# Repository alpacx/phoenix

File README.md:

# Phoenix — gateway multi-piattaforma

Gateway sperimentale, non ancora un prodotto validato. Backend ESP32 esistente;
backend Linux per ROCK 4C+ implementato in forma sperimentale e testato in Docker. La sezione hardware/build sotto descrive
ESP32; per Linux consultare il relativo README e le verifiche disponibili.

## Organizzazione

- [ESP32 / ESP-IDF](platforms/esp32/README.md): sorgenti in `platforms/esp32/main/`.
- [Linux / ROCK](platforms/linux/README.md): backend Linux, istruzioni e stato delle verifiche.
- `shared/web/`: pannello amministrativo comune.
- `shared/phoenix_core/`: logica C portabile.
- [Mappa del progetto](docs/PROJECT_STRUCTURE.md) e [istruzioni agenti](AGENTS.md).
- `hardware/phoenix-g1/`: progettazione della scheda custom, ancora incompleta.

Implementati: Ethernet IP101/RMII con DHCP, USB HS CDC-NCM con DHCP/NAT IPv4,
firewall L3/L4, API amministrativa locale e pannello, importatore WireGuard IPv4
full tunnel e blocco in uscita, gestione C6 STA/AP e aggiornamento firmato in software. La presenza del codice e una build riuscita non
provano il funzionamento sul banco: consultare PROGRESS.md.

## Build

ESP-IDF 5.5.4, commit esatto `10ca0dff2f40aeb539f22d1ef88d031cf7421743`.
Dipendenze registry e relativi hash in dependencies.lock. Toolchain installata:
`riscv32-esp-elf esp-14.2.0_20260121`. Script configurato per l'ambiente locale;
IDF_PATH e IDF_PYTHON_ENV_PATH sono sovrascrivibili.

```sh
./tools/test.sh
# Scheda rilevata v3.1; USB dati spento:
./tools/build.sh -B build-rev3 -D SDKCONFIG=build-rev3/sdkconfig \
  -D 'SDKCONFIG_DEFAULTS=sdkconfig.defaults;sdkconfig.rev3'
# Solo compilazione del percorso USB, NON certifica il cablaggio:
./tools/build.sh -B build-usb-rev3 -D SDKCONFIG=build-usb-rev3/sdkconfig \
  -D 'SDKCONFIG_DEFAULTS=sdkconfig.defaults;sdkconfig.rev3;sdkconfig.lab;sdkconfig.signed'
```

La variante firmata richiede prima la chiave descritta in [OTA](docs/OTA.md).

Il default sdkconfig.defaults supporta P4 v1.x; non caricarlo sulla v3.1.
Per una build USB di banco v3.x aggiungere sdkconfig.lab DOPO sdkconfig.rev3
in una cartella di build nuova. Non modificare i file SDK globali.

## Cablaggio e flash

Leggere [HARDWARE.md](docs/HARDWARE.md). La USB-C è seriale/alimentazione; la
Type-A è OTG e porta VBUS generata dalla scheda. Non collegare un generico
cavo host-host. USB dati resta disattivata per default.

Il backup originale è locale, riservato e ignorato da Git:
`results/recovery/original-flash.bin`. Non distribuirlo: può contenere dati
preesistenti. Per ripristinare, dopo aver identificato nuovamente la stessa
scheda e verificato hash/dimensione:

```sh
# Da ambiente ESP-IDF attivato. PORT deve essere la P4 dedicata identificata.
python -m esptool --chip esp32p4 --port "$PORT" write_flash 0 results/recovery/original-flash.bin
```

Non modificare eFuse. Nessuna flash encryption/secure boot irreversibile attivata.
BOOT+RESET è la via ROM di recupero; BOOT condivide GPIO35 con Ethernet TXD1:
non usarlo come pulsante dell'interfaccia durante il traffico.

## Uso sperimentale

USB LAN: 192.168.7.1/24, DHCP, pannello http://192.168.7.1/. Nessun servizio
amministrativo accettato dall'uplink. Pairing via UART nei primi 120 secondi:
`pair ` seguito da 64 caratteri esadecimali casuali, mai riportati nei log.
Il token rimane solo nel client; la scheda conserva SHA-256 in NVS.
`time <epoch UNIX di 10 cifre>` imposta l'orologio nello stesso intervallo.
Il pannello conserva il token nella sessionStorage della scheda browser e lo elimina al logout.

All'avvio il traffico inoltrato è bloccato. La modalità diretta è una scelta
esplicita via API. WireGuard resta chiuso finché non esiste una sessione valida.
Il dispositivo non controlla il traffico del Mac sulle altre interfacce.
Non è un antivirus, un IDS completo o uno strumento di ispezione HTTPS.

[API](docs/API.md) · [Architettura](docs/ARCHITECTURE.md) ·
[Prove](docs/TESTING.md) · [Dipendenze](docs/DEPENDENCIES.md) ·
[Attività](TASKS.md) · [Ripresa](NEXT_SESSION.md)

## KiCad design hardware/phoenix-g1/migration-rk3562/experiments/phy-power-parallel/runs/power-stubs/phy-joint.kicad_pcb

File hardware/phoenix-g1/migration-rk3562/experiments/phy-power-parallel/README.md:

# PHY joint SW geometry — isolated, electrically unqualified

This experiment freezes compact-corridor source `21c11942a68f62c506769caed42e84f3358d85e159f8b7bc2ba2f87e9014b30f`. No main board, main checkpoint or original compact study was modified.

`checkpoint.json` selects joint-002 for **geometry study only**. Its SW trunk and output branch remain 1.55 mm, clearance rules remain unchanged, input corridor remains 1.05 mm. RXCLK resistor return is relocated to the already-tested main-route corridor ending at (66.15,30.125), maintaining 0.20 mm track and 0.45/0.20 mm via. The output branch termination is offset 0.15 mm within L501 pad 2; this removes the 0.10 mm inter-branch clearance failure without narrowing either branch.

Joint-001 exposed a further clearance to U5 NC pad31 (0.0735 mm). Joint-002 moves the broad SW trunk outward/upward and extends the existing exploratory pin fanout. This removes all new DRC errors, but the 0.20 mm QFN neck is 0.707 mm long and **does not satisfy the historical >60 mil whole-path guidance**. No permission/derogation to that guidance is inferred. Do not promote this route as qualified power layout.

Verification: zero new DRC violations; 2,006 pad instances and 5,810 unreplaced tracks/vias preserved; 71 original connected pad groups preserved; no new mechanical reservation conflicts. U5.30→L501.1, L501.2→C511.1, R522.2→C515.2 and C515.1→C517.1 connectivity passes. Six subprocess tests exercise nominal routes, intentional width reductions, SW/output disconnections and mandatory qualification hold.

Rebuild with KiCad Python:

```
python3 hardware/phoenix-g1/tools/parallel_phy_sw_joint.py --case joint-rebuild
python3 hardware/phoenix-g1/tools/parallel_phy_test_joint.py
```

Use KiCad bundled Python, not generic system Python. Test script checks frozen joint-002 hash; rebuild receives new UUIDs and has its own report. Each report compares actual geometry with the frozen baseline. Existing baseline DRC items remain; “zero new” does not mean production-ready.

Remaining electrical holds: applicable Realtek fanout guidance, compact inductor saturation/DCR/ripple, effective C515 capacitance at 3.3 V (component review indicates strong DC bias reduction), and remaining input/load feeds. No simulation or physical test has been performed. No BOM adoption, purchase or manufacturing release.

## Follow-up component and feed probes

`variant-16v.json` records a second geometry-passing, six-test-passing candidate using CL10A475KO8NNNC (C19666) for C515, with unchanged 0603 footprint. Component-review Samsung numeric curves indicate 3.2694 µF typical at 3.3 V; this is an improvement over approximately 2.10 µF for C1705, **not** a guaranteed effective minimum or validation of regulator stability. Rebuild using `--bulk-16v --case joint-16v-rebuild`. Test via `PHOENIX_PHY_TEST_VARIANT=joint-16v`.

The 0805 candidate CL21A475KAQNNNE (C1779) was physically substituted in `runs/joint-0805` and rejected: GND copper at y=23.3 and courtyards R509/R1002/R516 interfere. Do not treat it as a drop-in. `bulk-0805-review.json` lists the required surrounding layout changes.

Two explicitly drawn full-width F.Cu feed candidates are retained as rejected evidence: `feed-front` (R530 to C515,1.05 mm,19 new violations) and `load-front` (C511 to C512,1.55 mm,84 new violations). These specific paths intersect existing oscillator, buck feedback, bypass and strap copper. They do not prove that all possible F.Cu paths are impossible. Do not repeat them or adopt them. `parallel_phy_feed_probe.py` reproduces both without modifying the baseline or reducing widths.

## Post-inductor distribution geometry

`load-checkpoint.json` records C511.1→C512.1 continuity via a full 1.55 mm In3.Cu corridor and two 0.60/0.30 mm through vias at each end. The north2 path avoids the CPU via at (56.5,28.5) found by the north1 probe; the southern path remains rejected due to oscillator/ground vias. No new traces are placed on In1/In4 ground planes. Zero new DRC violations, all 5,822 incoming copper items and 72 connected pad groups preserved, no new mechanical conflicts. Six tests include width reduction, cutting either via array, ground-plane role and mandatory qualification holds.

This is **post-inductor distribution**, not a relaxation of the unresolved REG_OUT/DVDD33 local no-via/width guidance. Via current capacity, power integrity, return paths, thermal performance and pad-overlap/filled-via assembly requirements remain unqualified. No fabrication release. `parallel_phy_feed_probe.py load-in3-north2` rebuilds this geometry; `parallel_phy_test_load.py` checks it.

### Additional bypasses

`load-c514-checkpoint.json`: extends the In3 1.55 mm distribution to C514/U5.21, with two 0.60/0.30 mm load vias. Six tests pass; zero new DRC, all incoming copper preserved. The earlier y=29.0/29.1 paths fail against the RXCLK GND via; final trunk y=28.9 gives 0.225 mm nominal clearance.

`load-c513-checkpoint.json`: moves previously disconnected C513 from its remote position to (65.4,34.5), beside U5.8, preserving pad identities and nets. Replaces only its two explicitly identified disconnected ground-stub segments. Adds the 1.55 mm In3 branch and two 0.60/0.30 mm vias, a 0.20 mm F.Cu pin fanout, and a 0.20 mm local GND return with a 0.45/0.20 mm via. Both C513 terminals are verified connected, including U5.8→C513.1 and C513.2→existing GND. Zero new DRC and six tests pass; mandatory fanout/current/PI/via-overlap holds remain. Courtyard placement is tight between U5 and U22; manufacturability remains to be reviewed. The rejected vertical and first horizontal placements are retained in c513/c513b reports.

No main/BOM adoption has occurred. The latest geometry candidate is an isolated study, not a replacement for the main checkpoint. C522/U5.38 and upstream input feed remain incomplete.

## Rebuild and C522 blockers

`rebuild-verification.json` confirms a fresh C513d rebuild matches all footprint identities/placements, pad UUIDs/nets/sizes and track/via geometry (generated copper UUIDs and zone serialization excluded). Fresh DRC/preservation/connectivity also pass. Rebuild does not overwrite the selected study: set `PHOENIX_PHY_OUTPUT_CASE=rebuild-c513d` when calling its builder.

C522 studies `c522-clock` and `c522-clock2` remain rejected. The first relocates the capacitor behind the board and replaces XOUT, but collides with Y501 pad, the existing +5V_MAIN trunk on In2, and clock copper. The second also replaces the B.Cu XIN branch at its original 0.20 mm width; single-via escape and broad power still collide with the local ground/clock corridor. Neither candidate is selected. Clock loading/loop geometry and any changed via strategy would require qualification even after geometric success. Moving C511 local return or the upstream 5V corridor would be a broader joint change; no such change was made here.

## Sequential continuation — 18 November, 16V bulk carried forward

`load-c513-16v-checkpoint.json` is the latest isolated geometry variant. It carries the previously studied C515 CL10A475KO8NNNC into the C513 bypass/distribution candidate. No copper geometry or footprint placement changes were made in this variant. DRC introduces no violations; preservation and nine required connectivity checks pass. Six load tests pass, including deliberate route narrowing and disconnections. Current public C19666 lookup: $0.015, presale 2503304 / overseas 3310825; not assembly allocation. Typical 3.2694uF at 3.3V is not a guaranteed minimum or stability qualification. No main-board/BOM adoption.

New `input-in2-001` upstream feed probe was rejected: full 1.05mm inner route collides with +3V3_IO and WIFI_BUCK_OUT; entry/exit also collide with the oscillator ground and CPU_BUCK_EN. Do not run the untried `input-in2-002` as a proposed fix: moving the middle path does not solve endpoint conflicts. The input needs a joint redesign of the existing R530 entry and C2007/Y2001 ground corridor and a different C515 via escape. R530 input pad is already connected, so moving it without restoring its incoming branch is not acceptable. No reduced widths or clearance rules.

## Upstream PHY supply and pin 38, 19 November

The isolated board in `phy-upstream-verified.json` supplies C515 from R530 with 1.05 mm copper. The new In2.Cu route totals 27.44 mm including the array connections. The oscillator supply and ground branches were rerouted. The audit compares the saved board with input-ground-local-002, checks pad groups and explicit copper replacements, and finds no new DRC items or mount conflicts. Removing either single via at either end retains connectivity. Removing both vias at either end interrupts the feed. Review DC drop, transient response, oscillator return, and capacitor land/via manufacturability before adoption. The compact inductor and effective capacitance remain subject to electrical qualification.

Reproduce the upstream path with `phy_offset_link.py --reroute --array --ground reuse`, `phy_bulk_corridor.py --detour --east`, then `phy_verify_bulk.py`. Use the KiCad Python interpreter for these scripts and a Python 3 interpreter with Shapely on PATH for the grid search.

The downstream experiment reroutes the oscillator input/output at their inherited widths. The pin-38 via connects to a rear C522 bypass in `c522-local-bypass.json`. Its return reaches an existing ground via. That stage still requires a supply branch from C511. Clock loading, bypass-loop inductance, and clearances under assembly tolerances remain to be qualified.

The subsequent integrated candidate in `c522-verified.json` also connects C511 to C522 and PHY pin 38. C522 is on the rear at (61.3,32.1). Its ground terminal connects to an existing return via. The new rear 1.55 mm branch reaches the existing C513 via pair. Cutting either individual via preserves the C522 supply and cutting both opens it in the CAD connectivity graph. The 0.20 mm local pin escape, changed crystal routing and return length require electrical review. Pin continuity and geometric checks do not qualify regulator stability.

The reproducible chain after the upstream route is `phy_pin38_escape.py`, `phy_c522_rear.py --local --new-return --wide`, `phy_c522_joint_sites.py`, `phy_c522_return.py --joint`, then `phy_verify_c522.py`.

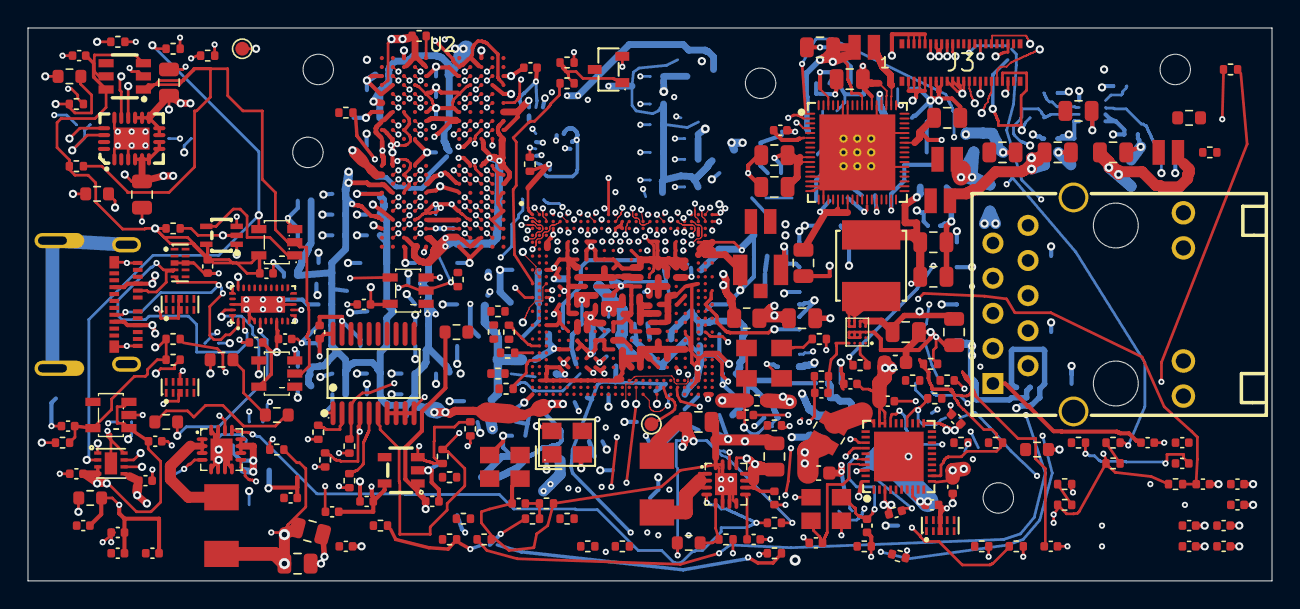
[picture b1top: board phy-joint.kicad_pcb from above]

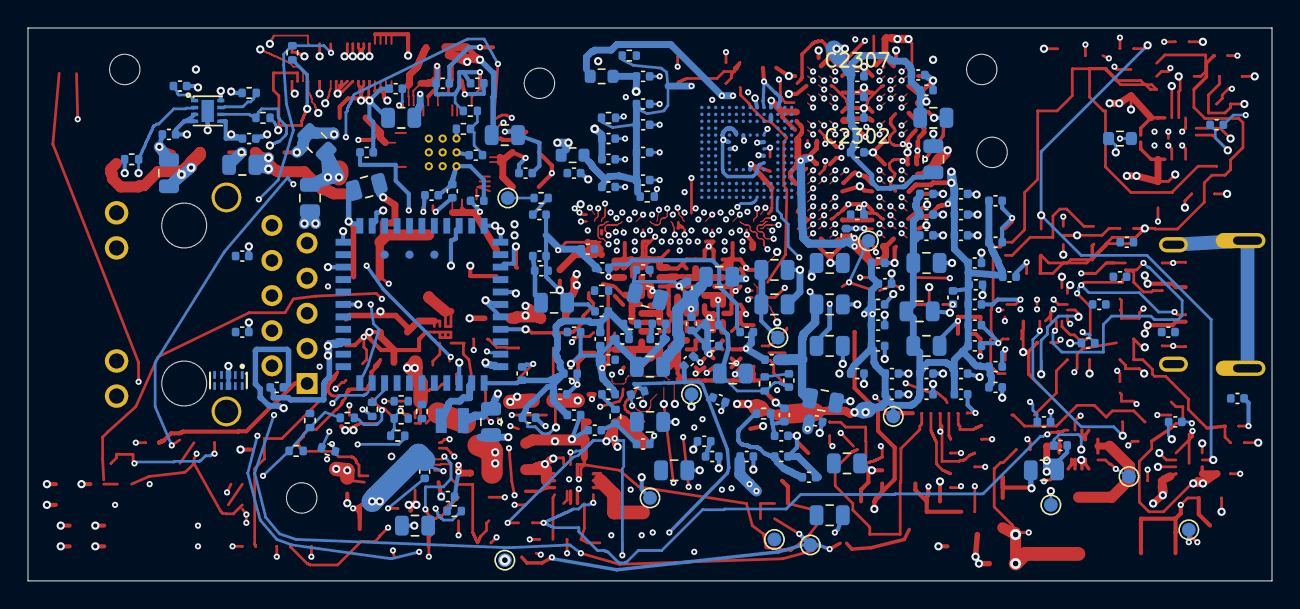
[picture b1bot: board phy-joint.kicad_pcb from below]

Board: 6 copper layers, 90.0 x 40.0 mm, 378 parts (187 on the bottom side), 277 nets.

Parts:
C410, C411, C412, C451, C452, C454, C501, C512, C513, C514, C516, C517, C518, C522, C1103, C1104, C1105, C1106, C1107, C1503, C1811, C2007, C2302, C2303, C2304, C2306, C2307, C2308: 100n; C_0402_1005Metric
C413, C414, C415, C519, C8101, C8102: 1u; C_0402_1005Metric
C421, C422, C423, C424, C425, C431, C432, C433, C434, C435, C441, C442, C443, C444, C445, C1304, C1305, C1603, C1604, C1605, C1606, C1607, C1608, C1613, C1614, C1618, C1619, C1622, C1623, C2204: 22u / 10V; C_0805_2012Metric
C460, C461, C462, C463, C464, C465, C466, C467, C468, C469, C480, C481, C482, C483, C484, C485, C531, C1101, C1201, C1203, C1611, C1612, C1626, C1628, C1630, C1632, C1634, C1636, C1680, C1682, C1801, C1812, C2005: 1u / 10V; C_0402_1005Metric
C470, C1301, C1615, C1620, C1624, C1650, C1664, C1678, C2201: 10u / 10V; C_0805_2012Metric
C511: 4.7uF CL10A475KP8NNNC CANDIDATE; C_0603_1608Metric
C515: 4.7uF CL10A475KO8NNNC CANDIDATE 16V; C_0603_1608Metric
C520, C521, C1501, C1502: 20p C0G / tune; C_0402_1005Metric
C601, C602, C603, C604, C605: 100n / 16V X7R; C_0402_1005Metric
C606: 100n / 10V X7R; C_0402_1005Metric
C1001, C1002, C1011, C1012, C1013, C1014: 22u / 10V X5R; C_0805_2012Metric
C1020: 1u / 10V X5R; C_0402_1005Metric
C1102, C1802: 2.2u / 10V; C_0402_1005Metric
C1202: 22n / 10V; C_0402_1005Metric
C1302, C1601, C1609, C1616, C1621, C1625, C1627, C1629, C1631, C1633, C1635, C1637, C1638, C1639, C1640, C1641, C1642, C1643, C1644, C1645, C1646, C1647, C1651, C1652, C1653, C1654, C1655, C1656, C1657, C1658, C1659, C1660, C1661, C1662, C1665, C1666, C1667, C1668, C1669, C1670, C1671, C1672, C1673, C1674, C1675, C1676, C1679, C1681, C1683: 100n / 10V; C_0402_1005Metric
C1303: 10n / 10V; C_0402_1005Metric
C1602, C1610, C1617, C1648, C1649, C1663, C1677: 4.7u / 10V; C_0402_1005Metric
C1901, C1902: 1u / 25V X7R; C_0805_2012Metric
C1903: 1n / C0G; C_0402_1005Metric
C2001: 22u / 6.3V; C_0805_2012Metric
C2002, C2006, C2202: 100n / 16V; C_0402_1005Metric
C2003: 4.7u / 6.3V; C_0805_2012Metric
C2004: 4.7u / 6.3V; C_0402_1005Metric
C2008, C2009: 8p C0G; C_0402_1005Metric
C2203: 1n / 10V; C_0402_1005Metric
C2301, C2305: 10u; C_0805_2012Metric
C8001: 2.2u candidate; C_0402_1005Metric
C8002, C8003, C8004, C8005, C8007, C8008: 100n candidate; C_0402_1005Metric
C8006, C8009: 4.7u candidate; C_0402_1005Metric
C8010: 100n VCCIO2 at SoC candidate; C_0402_1005Metric
C8103: 22n; C_0402_1005Metric
FB2001: 100R @100MHz / 4A; R_0805_2012Metric
H8101, H8102, H8103, H8104, H8105: MountingHole_2.2mm_M2
J1: 2012670005; USB_C_Molex_2012670005
J2: HR911130A; RJ45-TH_HR911130A
J3: DF40C-40DP-0.4V(51); DF40C_40DP_0.4V
J2001: U.FL-R-SMT-1; Hirose_UFL_R_SMT_1_80
L401, L402, L403, L404, L405: 470nH; L_APH201610
L501: 2.2uH DCR65m max CANDIDATE; L_AFE252012
L1001: 240nH - candidate; IND-SMD_L5.0-W5.0-PRS5020-330MT
L1301, L2201: 2.2uH DCR35m max; L_APH0518
L2001: 2.2uH / 2.4A Isat at 20C; Murata_DFE201610E
Q1: MMBT3904-C20526; SOT-23-3_L2.9-W1.3-P1.90-LS2.4-BR
R201: 240R 1%; R_0402_1005Metric
R410: 180k 1%; R_0402_1005Metric
R411, R1505, R2203: 100k 1%; R_0402_1005Metric
R412, R413, R516, R1504, R2002: 10k; R_0402_1005Metric
R414, R415, R501, R502, R503, R504, R505, R506, R507, R508, R509, R510, R511, R512, R515, R1501, R2003: 22R; R_0402_1005Metric
R416, R417: 2.2k; R_0402_1005Metric
R421, R422, R424, R2004: 100R; R_0402_1005Metric
R431: 45.3k 0.1%; R_0603_1608Metric
R432: 121k 0.1%; R_0603_1608Metric
R513: 2.49k 1%; R_0402_1005Metric
R514: 1.5k; R_0402_1005Metric
R521, R522, R523, R524, R525, R526, R527, R528, R529, R2101, R2102: 4.7k; R_0402_1005Metric
R530: 0R - power link; R_0402_1005Metric
R601, R605, R606: 300k 0.1% 25ppm; R_0603_1608Metric
R602, R603, R604: 200k 1%; R_0402_1005Metric
R1001: 100R 1%; R_0402_1005Metric
R1002: 51k 1%; R_0402_1005Metric
R1101, R1103, R1202, R1301, R1804, R2201, R8102, R8103: 100k; R_0402_1005Metric
R1102, R1802, R1811, R1812, R1813, R1814, R1815, R2010, R2011, R2012, R2013, R2014, R2103, R2104: 47k; R_0402_1005Metric
R1201: 806R 1%; R_0603_1608Metric
R1502: 1M; R_0402_1005Metric
R1503: 120R 1%; R_0402_1005Metric
R1506: 1M 1%; R_0402_1005Metric
R1507: 0R; R_0402_1005Metric
R1601, R1602: 0R supply link; R_0402_1005Metric
R1801: 1k; R_0402_1005Metric
R1803: 180R 1%; R_0603_1608Metric
R1901: 35.7k 0.1% 25ppm; R_0603_1608Metric
R1902, R1904: 10k 0.1% 25ppm; R_0402_1005Metric
R1903: 47.5k 0.1% 25ppm; R_0603_1608Metric
R1905: 33.2k 1%; R_0603_1608Metric
R2001: 0R RF tuning; R_0402_1005Metric
R2202: 348k 1%; R_0603_1608Metric
R8001, R8002, R8003: 10k candidate; R_0402_1005Metric
R8004: 22R candidate; R_0402_1005Metric
R8005: 47k candidate; R_0402_1005Metric
R8006, R8007: 0R 0603 rail link candidate; R_0603_1608Metric
R8101: 2.1k candidate; R_0402_1005Metric
TP1: GND; TestPoint_Pad_D1.0mm
TP2: VBUS_RAW; TestPoint_Pad_D1.0mm
TP3: +5V_MAIN; TestPoint_Pad_D1.0mm
TP4: +3V3_SYS; TestPoint_Pad_D1.0mm
TP5: +3V3_PMU; TestPoint_Pad_D1.0mm
TP6: +3V3_IO; TestPoint_Pad_D1.0mm
TP7: +1V5_DDR; TestPoint_Pad_D1.0mm
TP8: VDD_CPU; TestPoint_Pad_D1.0mm
TP9: RESET_N; TestPoint_Pad_D1.0mm
TP10: RECOVERY_ADC; TestPoint_Pad_D1.0mm
TP11: DEBUG_RX; TestPoint_Pad_D1.0mm
TP12: DEBUG_TX; TestPoint_Pad_D1.0mm
TP13: USB_POWER_FAULT_N; TestPoint_Pad_D1.0mm
TP14: SYS_3V3_PG; TestPoint_Pad_D1.0mm
U1: RK3562; RK3562_FCCSP478_13.9mm_MIXED_PITCH_CANDIDATE
U2: H9HCNNN8KUMLHR-NME; H9HCNNN8KUMLHR_FBGA200_10x15_P0.8x0.65_DRAFT
U4: RK809-5; QFN-68_L7.0-W7.0-P0.35-BL-EP5.5
U5: RTL8211F-CG; WQFN-40_L5.0-W5.0-P0.4-BL-EP
U6: HD3SS3220IRNHR; WQFN-30_L4.5-W2.5-P0.4-BL-EP
U7, U8, U9: TPD4EUSB30DQAR; USON-10_L2.5-W1.0-P0.50-BL
U10: RK860-0; WLCSP-20_L2.0-W1.6-R5-C4-P0.40-TL
U11: TLV75533PDBVR; SOT-23-5_L3.0-W1.7-P0.95-LS2.8-BR
U12: TPS3808G33DBVR; SOT-23-6_L2.9-W1.6-P0.95-LS2.8-BR
U13, U16: SN74LVC1G04DBVR; SOT-23-5_L3.0-W1.7-P0.95-LS2.8-BR
U14: SN74LVC1G02DCKR; SC-70-5_L2.1-W1.3-P0.65-LS2.1-BR
U15, U8101: TPS259531DSGR; WSON-8_L2.0-W2.0-P0.50-TL-EP
U17: TPS62132RGTR; VQFN-16_L3.0-W3.0-P0.50-TL-EP
U19: SN74LVC1G08DBVR; SOT-23-5_L3.0-W1.7-P0.95-LS2.8-BR
U20: TPS7A2030PDBVR; TSOT-23-5_L2.9-W1.6-P0.95-LS2.8-BR
U21: SN74LVC541APWR_C113281; TSSOP-20_L6.5-W4.4-P0.65-LS6.4-BL
U22, U23: TPD4E05U06DQAR; USON-10_L2.5-W1.0-P0.50-BL
U24: TPS25940ARVCR; WQFN-20_L4.0-W3.0-P0.50-BL-EP
U25: AP6256; AP6256_12x12_P0.9
U26: TPS62130RGTR; VQFN-16_L3.0-W3.0-P0.50-TL-EP
U8001: KLM8G1GETF_B041_DRAFT; Samsung_FBGA153_11.5x13_P0.5_DRAFT
Y1: 24MHz CL12pF ESR40R; Crystal_3225_JWT
Y501: 25MHz CL12pF; Crystal_3225_YXC
Y2001: OVETDLJANF-32.768KHZ; Taitien_OV_5032
Y2002: X1E0000210877; CRYSTAL-SMD_4P-L3.2-W2.5-BL

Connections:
+1V0_PHY: C511.1, C512.1, C513.1, C514.1, C522.1, L501.2, U5.3, U5.8, U5.21, U5.38
+1V1_LPDDR4: C433.1, C443.1, C1646.1, C1647.1, C1648.1, C1649.1, C1650.1, C1651.1, C1652.1, C1653.1, C1654.1, C1655.1, C1656.1, C1657.1, C1658.1, C1659.1, C1660.1, C1661.1, C1662.1, C1663.1, C1664.1, C1665.1, C1666.1, C1667.1, C1668.1, C1669.1, C1670.1, C1671.1, C1672.1, C1673.1, C1674.1, C1675.1, C1676.1, C1677.1, C1678.1, L403.2, R201.2, R431.1, R1503.2, TP7.1, U1.1D6, U1.1D11, U1.1E3, U1.1E4, U1.1E5, U1.1E6, U1.1E7, U1.1E8, U1.1E9, U1.1E10, U2.A4, U2.A9, U2.AA3, U2.AA5, U2.AA8, U2.AA10, U2.AB4, U2.AB9, U2.B3, U2.B5, U2.B8, U2.B10, U2.D1, U2.D5, U2.D8, U2.D12, U2.F3, U2.F5, U2.F8, U2.F10, U2.G2, U2.H1, U2.H5, U2.H8, U2.H12, U2.K1, U2.K3, U2.K10, U2.K12, U2.N1, U2.N3, U2.N10, U2.N12, U2.R1, U2.R5, U2.R8, U2.R12, U2.T2, U2.U3, U2.U5, U2.U8, U2.U10, U2.W1, U2.W5, U2.W8, U2.W12, U4.26
+1V8_SYS: C435.1, C445.1, C2301.1, C2302.1, C2303.1, C2304.1, C2305.1, C2306.1, C2307.1, C2308.1, L405.2, R8006.1, U2.F1, U2.F12, U2.G4, U2.G9, U2.T4, U2.T9, U2.U1, U2.U12, U4.59
+3V0_LCD: C1802.1, C1811.1, C1812.1, U20.5, U21.20
+3V3_AON: C606.1, C1102.1, C1103.1, C1104.1, C1105.1, C1106.1, C1107.1, R602.1, R603.1, R604.1, R1101.1, R1202.2, U6.8, U11.5, U12.3, U12.5, U12.6, U13.5, U14.5, U16.5, U19.5
+3V3_IO: C470.1, C1627.1, C1628.1, C1637.1, C1638.1, C1639.1, C1640.1, C1641.1, C1683.1, C2004.1, C2005.1, C2006.1, C2007.1, J3.36, R530.1, R1505.1, R1804.1, R1815.2, R2010.2, R2011.2, R2012.2, R2013.2, R2014.2, R2101.2, R2102.2, R8007.1, R8102.2, TP6.1, U1.1G15, U1.1H14, U1.1K3, U1.1L3, U1.1L5, U1.1M4, U1.1M14, U4.55, U20.3, U25.22, Y2001.1, Y2001.4
+3V3_PHY: C515.1, C516.1, C517.1, C518.1, C519.1, R514.2, R521.2, R525.2, R526.2, R527.2, R530.2, U5.11, U5.28, U5.29, U5.40
+3V3_PMU: C465.1, C1625.1, C1626.1, R412.1, R413.1, R416.1, R417.1, R1002.1, R2103.2, R2104.2, TP5.1, U1.1L11, U1.1L12, U4.31
+3V3_SD: C469.1, U4.58
+3V3_SYS: C421.1, C422.1, C423.1, C424.1, C425.1, C480.1, C481.1, C482.1, C483.1, C484.1, C485.1, C1304.1, C1305.1, L1301.2, R410.1, R1301.2, TP4.1, U4.4, U4.10, U4.11, U4.22, U4.24, U4.30, U4.33, U4.45, U4.54, U4.57, U4.66, U17.14
+3V58_WIFI: C2204.1, FB2001.1, L2201.2, R2201.2, R2202.1, U26.14
+5V_ADDON: C8102.1, J3.1, J3.2, J3.3, J3.4, J3.5, J3.6, J3.7, J3.8, U8101.5
+5V_MAIN: C1001.1, C1002.1, C1203.1, C1301.1, C1302.1, C1801.1, C2201.1, C2202.1, C8101.1, R1803.1, TP3.1, U10.D1, U10.D2, U10.E1, U10.E2, U15.5, U17.10, U17.11, U17.12, U20.1, U26.10, U26.11, U26.12, U26.13, U8101.3, U8101.4
ADDON_DVDT: C8103.1, U8101.1
ADDON_ILIM: R8101.1, U8101.7
ADDON_USB_DM: J3.21, U1.AE26
ADDON_USB_DP: J3.19, U1.AE27
AON_READY: R1101.2, U12.1, U13.2, U19.2
CC_OUT1_N: R603.2, U6.25, U14.1
CC_OUT2_N: R604.2, U6.26, U14.2
CC_VBUS_SENSE: R606.2, U6.5
CC_VBUS_SERIES_1: R601.2, R605.1
CC_VBUS_SERIES_2: R605.2, R606.1
CHASSIS: J2.P10, J2.SHIELD0, J2.SHIELD1
CPU_BUCK_EN: R1002.2, U10.A2
CPU_FB_SENSE: C1020.2, R1001.2, U10.A4
CPU_SW: L1001.1, U10.D3, U10.D4, U10.E3, U10.E4
DDR_FB: R431.2, R432.1, U4.27
DDR_RZQ: R1503.1, U1.1D4
DEBUG_RX: TP11.1, U1.AF20
DEBUG_TX: TP12.1, U1.AE20
EMMC_3V3: C8007.1, C8008.1, C8009.1, R8007.2, U8001.E6, U8001.F5, U8001.J10, U8001.K9
EMMC_CLK: R8004.2, U8001.M6
EMMC_CMD: R8002.2, U1.M26, U8001.M5
EMMC_D0: R8001.2, U1.J25, U8001.A3
EMMC_D1: U1.J26, U8001.A4
EMMC_D2: U1.H25, U8001.A5
EMMC_D3: U1.K27, U8001.B2
EMMC_D4: U1.K26, U8001.B3
EMMC_D5: U1.K25, U8001.B4
EMMC_D6: U1.H26, U8001.B5
EMMC_D7: U1.H27, U8001.B6
EMMC_IO_1V8: C8002.1, C8003.1, C8004.1, C8005.1, C8006.1, C8010.1, R8001.1, R8002.1, R8003.1, R8006.2, U1.1F14, U8001.C6, U8001.M4, U8001.N4, U8001.P3, U8001.P5
EMMC_RESET_N: R8003.2, U8001.K5
EMMC_STRB: R8005.1, U1.L26, U8001.H5
EMMC_VDDI: C8001.1, U8001.C2
ETH_CENTER_TAP: C531.1, J2.P1
ETH_MDC: U1.AC1, U5.13
ETH_MDI0_N: J2.P3, U5.2, U22.2
ETH_MDI0_P: J2.P2, U5.1, U22.1
ETH_MDI1_N: J2.P7, U5.5, U22.5
ETH_MDI1_P: J2.P4, U5.4, U22.4
ETH_MDI2_N: J2.P6, U5.7, U23.2
ETH_MDI2_P: J2.P5, U5.6, U23.1
ETH_MDI3_N: J2.P9, U5.10, U23.5
ETH_MDI3_P: J2.P8, U5.9, U23.4
ETH_MDIO: R514.1, U1.AC2, U5.14
ETH_RESET_GPIO_N: R515.1, U1.T2
ETH_RXCLK: R512.1, U1.U2
ETH_RXD0: R507.1, U1.W3
ETH_RXD1: R508.1, U1.W1
ETH_RXD2: R509.1, U1.W2
ETH_RXD3: R510.1, U1.Y3
ETH_RXDV_CRS: R511.1, U1.V2
ETH_TXCLK: R506.1, U1.Y2
ETH_TXD0: R501.1, U1.AA1
ETH_TXD1: R502.1, U1.AA2
ETH_TXD2: R503.1, U1.AB3
ETH_TXD3: R504.1, U1.AB2
ETH_TXEN: R505.1, U1.AA3
EXP_GPIO0: J3.27, R8103.1, U1.K2, U8101.2
EXP_GPIO1: J3.28, R8102.1, U1.L3, U8101.6
EXP_GPIO2: J3.29, U1.K3
EXP_GPIO3: J3.30, U1.L2
EXP_I2C_SCL: J3.24, R2102.1, U1.AF16
EXP_I2C_SDA: J3.23, R2101.1, U1.AE15
EXP_SPI_CLK: J3.31, U1.AE16
EXP_SPI_CS0_N: J3.34, R2103.1, U1.AG17
EXP_SPI_CS1_N: J3.35, R2104.1, U1.AF15
EXP_SPI_MISO: J3.33, U1.AE18
EXP_SPI_MOSI: J3.32, U1.AG19
EXP_UART_RX: J3.26, U1.Y25
EXP_UART_TX: J3.25, U1.Y26
GND: C410.2, C411.2, C412.2, C413.2, C414.2, C415.2, C421.2, C422.2, C423.2, C424.2, C425.2, C431.2, C432.2, C433.2, C434.2, C435.2, C441.2, C442.2, C443.2, C444.2, C445.2, C460.2, C461.2, C462.2, C463.2, C464.2, C465.2, C466.2, C467.2, C468.2, C469.2, C470.2, C480.2, C481.2, C482.2, C483.2, C484.2, C485.2, C501.2, C511.2, C512.2, C513.2, C514.2, C515.2, C516.2, C517.2, C518.2, C519.2, C520.2, C521.2, C522.2, C531.2, C605.2, C606.2, C1001.2, C1002.2, C1011.2, C1012.2, C1013.2, C1014.2, C1101.2, C1102.2, C1103.2, C1104.2, C1105.2, C1106.2, C1107.2, C1201.2, C1202.2, C1203.2, C1301.2, C1302.2, C1303.2, C1304.2, C1305.2, C1501.2, C1502.2, C1503.2, C1601.2, C1602.2, C1603.2, C1604.2, C1605.2, C1606.2, C1607.2, C1608.2, C1609.2, C1610.2, C1611.2, C1612.2, C1613.2, C1614.2, C1615.2, C1616.2, C1617.2, C1618.2, C1619.2, C1620.2, C1621.2, C1622.2, C1623.2, C1624.2, C1625.2, C1626.2, C1627.2, C1628.2, C1629.2, C1630.2, C1631.2, C1632.2, C1633.2, C1634.2, C1635.2, C1636.2, C1637.2, C1638.2, C1639.2, C1640.2, C1641.2, C1642.2, C1643.2, C1644.2, C1645.2, C1646.2, C1647.2, C1648.2, C1649.2, C1650.2, C1651.2, C1652.2, C1653.2, C1654.2, C1655.2, C1656.2, C1657.2, C1658.2, C1659.2, C1660.2, C1661.2, C1662.2, C1663.2, C1664.2, C1665.2, C1666.2, C1667.2, C1668.2, C1669.2, C1670.2, C1671.2, C1672.2, C1673.2, C1674.2, C1675.2, C1676.2, C1677.2, C1678.2, C1679.2, C1680.2, C1681.2, C1682.2, C1683.2, C1801.2, C1802.2, C1811.2, C1812.2, C1901.2, C1902.2, C1903.2, C2001.2, C2002.2, C2003.2, C2004.2, C2005.2, C2006.2, C2007.2, C2008.2, C2009.2, C2201.2, C2202.2, C2203.2, C2204.2, C2301.2, C2302.2, C2303.2, C2304.2, C2305.2, C2306.2, C2307.2, C2308.2, C8001.2, C8002.2, C8003.2, C8004.2, C8005.2, C8006.2, C8007.2, C8008.2, C8009.2, C8010.2, C8101.2, C8102.2, C8103.2, J1.A1, J1.A12, J1.B1, J1.B12, J3.9, J3.10, J3.11, J3.12, J3.13, J3.14, J3.15, J3.16, J3.17, J3.18, J3.20, J3.22, J3.37, J3.38, J2001.2, J2001.3, Q1.2, R411.2, R432.2, R513.2, R516.2, R522.2, R523.2, R524.2, R528.2, R529.2, R1102.2, R1103.2, R1201.2, R1506.2, R1802.2, R1804.2, R1811.2, R1812.2, R1813.2, R1814.2, R1902.2, R1904.2, R1905.2, R2002.2, R2203.2, R8005.2, R8101.2, R8103.2, TP1.1, U1.1A2, U1.1A4, U1.1A5, U1.1A11, U1.1A12, U1.1A14, U1.1B2, U1.1B4, U1.1B5, U1.1B9, U1.1B12, U1.1B14, U1.1C1, U1.1C2, U1.1C3, U1.1C4, U1.1C5, U1.1C6, U1.1C7, U1.1C10, U1.1C11, U1.1C12, U1.1C13, U1.1C14, U1.1C15, U1.1D1, U1.1D2, U1.1D3, U1.1D7, U1.1D8, U1.1D9, U1.1D10, U1.1D12, U1.1D13, U1.1D14, U1.1D15, U1.1E1, U1.1E2, U1.1E11, U1.1E13, U1.1F1, U1.1F2, U1.1F3, U1.1F4, U1.1F5, U1.1F7, U1.1F9, U1.1F10, U1.1F15, U1.1G2, U1.1G6, U1.1G7, U1.1G9, U1.1G13, U1.1G14, U1.1H1, U1.1H2, U1.1H5, U1.1H9, U1.1H12, U1.1H13, U1.1J1, U1.1J2, U1.1J3, U1.1J4, U1.1J5, U1.1J8, U1.1J9, U1.1J13, U1.1K1, U1.1K4, U1.1K5, U1.1K6, U1.1K7, U1.1K8, U1.1K9, U1.1K11, U1.1K12, U1.1K13, U1.1L2, U1.1L4, U1.1L7, U1.1L9, U1.1L10, U1.1L15, U1.1M3, U1.1M5, U1.1M6, U1.1M12, U1.1N1, U1.1N2, U1.1N3, U1.1N4, U1.1N5, U1.1N6, U1.1N7, U1.1N8, U1.1N10, U1.1N11, U1.1N12, U1.1N13, U1.1N14, U1.1N15, U1.1P1, U1.1P2, U1.1P4, U1.1P5, U1.1P6, U1.1P8, U1.1P9, U1.1P10, U1.1P11, U1.1P13, U1.1R1, U1.1R2, U1.1R4, U1.1R5, U1.1R6, U1.1R8, U1.1R9, U1.1R10, U1.1R12, U1.1R14, U1.A1, U1.A12, U1.A16, U1.A27, U1.AA26, U1.AA27, U1.AB25, U1.AC3, U1.AD3, U1.AD25, U1.AE2, U1.AE3, U1.AE4, U1.AE5, U1.AE6, U1.AE7, U1.AE8, U1.AE9, U1.AE10, U1.AE11, U1.AE12, U1.AE13, U1.AE14, U1.AE21, U1.AE25, U1.AF24, U1.AG1, U1.AG15, U1.AG26, U1.AG27, U1.B14, U1.C3, U1.C4, U1.C7, U1.C9, U1.C13, U1.C14, U1.C15, U1.C19, U1.C21, U1.C24, U1.C25, U1.D2, U1.D25, U1.E3, U1.E25, U1.E26, U1.E27, U1.F3, U1.F25, U1.F26, U1.G25, U1.G26, U1.G27, U1.J3, U1.L25, U1.M27, U1.P26, U1.U3, U2.A3, U2.A10, U2.AB3, U2.AB5, U2.AB8, U2.AB10, U2.C1, U2.C5, U2.C8, U2.C12, U2.D2, U2.D4, U2.D9, U2.D11, U2.E1, U2.E5, U2.E8, U2.E12, U2.G1, U2.G3, U2.G5, U2.G8, U2.G10, U2.G12, U2.J1, U2.J3, U2.J10, U2.J12, U2.K2, U2.K4, U2.K9, U2.K11, U2.N2, U2.N4, U2.N9, U2.N11, U2.P1, U2.P3, U2.P10, U2.P12, U2.T1, U2.T3, U2.T5, U2.T8, U2.T10, U2.T12, U2.V1, U2.V5, U2.V8, U2.V12, U2.W2, U2.W4, U2.W9, U2.W11, U2.Y1, U2.Y5, U2.Y8, U2.Y12, U4.14, U4.15, U4.16, U4.17, U4.19, U4.40, U4.47, U4.56, U4.62, U4.63, U4.69, U5.41, U6.3, U6.4, U6.13, U6.28, U6.31, U7.3, U7.8, U8.3, U8.8, U9.3, U9.8, U10.B2, U10.B3, U10.B4, U10.C1, U10.C2, U10.C3, U10.C4, U11.2, U12.2, U13.3, U14.3, U15.8, U15.9, U16.3, U17.5, U17.6, U17.7, U17.8, U17.15, U17.16, U17.17, U19.3, U20.2, U21.1, U21.7, U21.8, U21.9, U21.10, U21.19, U22.3, U22.8, U23.3, U23.8, U24.1, U24.3, U24.16, U24.21, U25.1, U25.3, U25.6, U25.20, U25.26, U25.27, U25.28, U25.29, U25.31, U25.33, U25.34, U25.36, U25.43, U25.44, U26.6, U26.7, U26.8, U26.15, U26.16, U26.17, U8001.A6, U8001.C4, U8001.E7, U8001.G5, U8001.H10, U8001.J5, U8001.K8, U8001.N2, U8001.N5, U8001.P4, U8001.P6, U8101.8, U8101.9, Y1.2, Y1.4, Y501.2, Y501.4, Y2001.2, Y2002.2, Y2002.4
I2C0_SCL: R414.1, R416.2, U1.AG23, U10.A3
I2C0_SDA: R415.1, R417.2, U1.AE23, U10.B1
LCD_BL_BASE: Q1.1, R1801.2, R1802.1
LCD_BL_PWM: R1801.1, U1.L1
LCD_CS_N: R1815.1, U1.M3, U21.6
LCD_DC: R1813.1, U1.N1, U21.4
LCD_MOSI: R1811.1, U1.T3, U21.2
LCD_RESET_N: R1814.1, U1.N2, U21.5
LCD_SCLK: R1812.1, U1.N3, U21.3
LPDDR4_A0_A: U1.B10, U2.H2
LPDDR4_A0_B: U1.B18, U2.R2
LPDDR4_A1_A: U1.A10, U2.J2
LPDDR4_A1_B: U1.A18, U2.P2
LPDDR4_A2_A: U1.C10, U2.H9
LPDDR4_A2_B: U1.C18, U2.R9
LPDDR4_A3_A: U1.1A6, U2.H10
LPDDR4_A3_B: U1.1A10, U2.R10
LPDDR4_A4_A: U1.1B8, U2.H11
LPDDR4_A4_B: U1.1A9, U2.R11
LPDDR4_A5_A: U1.1A7, U2.J11
LPDDR4_A5_B: U1.1A8, U2.P11
LPDDR4_CKE0_A: U1.C12, U2.J4
LPDDR4_CKE0_B: U1.C16, U2.P4
LPDDR4_CLKN_A: U1.A13, U2.J9
LPDDR4_CLKN_B: U1.A15, U2.P9
LPDDR4_CLKP_A: U1.B13, U2.J8
LPDDR4_CLKP_B: U1.B15, U2.P8
LPDDR4_CS0N_A: U1.B11, U2.H4
LPDDR4_CS0N_B: U1.B17, U2.R4
LPDDR4_DM0_A: U1.B7, U2.C3
LPDDR4_DM0_B: U1.B21, U2.Y3
LPDDR4_DM1_A: U1.A2, U2.C10
LPDDR4_DM1_B: U1.A26, U2.Y10
LPDDR4_DQ0_A: U1.B6, U2.B2
LPDDR4_DQ0_B: U1.B22, U2.AA2
LPDDR4_DQ1_A: U1.B8, U2.C2
LPDDR4_DQ1_B: U1.B20, U2.Y2
LPDDR4_DQ2_A: U1.A8, U2.E2
LPDDR4_DQ2_B: U1.A20, U2.V2
LPDDR4_DQ3_A: U1.C8, U2.F2
LPDDR4_DQ3_B: U1.C20, U2.U2
LPDDR4_DQ4_A: U1.C5, U2.F4
LPDDR4_DQ4_B: U1.C23, U2.U4
LPDDR4_DQ5_A: U1.B5, U2.E4
LPDDR4_DQ5_B: U1.B23, U2.V4
LPDDR4_DQ6_A: U1.A6, U2.C4
LPDDR4_DQ6_B: U1.C22, U2.Y4
LPDDR4_DQ7_A: U1.C6, U2.B4
LPDDR4_DQ7_B: U1.A22, U2.AA4
LPDDR4_DQ8_A: U1.C2, U2.B11
LPDDR4_DQ8_B: U1.C26, U2.AA11
LPDDR4_DQ9_A: U1.C1, U2.C11
LPDDR4_DQ9_B: U1.C27, U2.Y11
LPDDR4_DQ10_A: U1.B1, U2.E11
LPDDR4_DQ10_B: U1.B27, U2.V11
LPDDR4_DQ11_A: U1.B2, U2.F11
LPDDR4_DQ11_B: U1.B26, U2.U11
LPDDR4_DQ12_A: U1.A4, U2.F9
LPDDR4_DQ12_B: U1.A24, U2.U9
LPDDR4_DQ13_A: U1.B4, U2.E9
LPDDR4_DQ13_B: U1.B24, U2.V9
LPDDR4_DQ14_A: U1.A3, U2.C9
LPDDR4_DQ14_B: U1.A25, U2.Y9
LPDDR4_DQ15_A: U1.B3, U2.B9
LPDDR4_DQ15_B: U1.B25, U2.AA9
LPDDR4_DQS0N_A: U1.1B3, U2.E3
LPDDR4_DQS0N_B: U1.1B13, U2.V3
LPDDR4_DQS0P_A: U1.1A3, U2.D3
LPDDR4_DQS0P_B: U1.1A13, U2.W3
LPDDR4_DQS1N_A: U1.1B1, U2.E10
LPDDR4_DQS1N_B: U1.1B15, U2.V10
LPDDR4_DQS1P_A: U1.1A1, U2.D10
LPDDR4_DQS1P_B: U1.1A15, U2.W10
LPDDR4_RESETN: U1.1B11, U2.T11
LPDDR4_ZQ_240R: R201.1, U2.A5
MUX_TX1_N: C602.1, U6.16
MUX_TX1_P: C601.1, U6.17
MUX_TX2_N: C604.1, U6.20
MUX_TX2_P: C603.1, U6.21
PHY_CFG_EXT: R527.1, U5.32
PHY_CFG_LDO0: R528.1, U5.33
PHY_CFG_LDO1: R529.1, U5.34
PHY_RESET_N: C501.1, R515.2, R516.1, U5.12
PHY_RSET: R513.1, U5.39
PHY_RXCLK: R512.2, R522.1, U5.27
PHY_RXD0: R507.2, R526.1, U5.25
PHY_RXD1: R508.2, R525.1, U5.24
PHY_RXD2: R509.2, R524.1, U5.23
PHY_RXD3: R510.2, R521.1, U5.22
PHY_RXDV_CRS: R511.2, R523.1, U5.26
PHY_SW: L501.1, U5.30
PHY_TXCLK: R506.2, U5.20
PHY_TXD0: R501.2, U5.18
PHY_TXD1: R502.2, U5.17
PHY_TXD2: R503.2, U5.16
PHY_TXD3: R504.2, U5.15
PHY_TXEN: R505.2, U5.19
PHY_XIN: C520.1, U5.36, Y501.1
PHY_XOUT: C521.1, U5.37, Y501.3
PMIC_1V8A: C414.1, U4.44
PMIC_1V8D: C415.1, U4.48
PMIC_INT_N: R413.2, U1.AF22, U4.7
PMIC_PWRON_N: C412.1, U4.52
PMIC_SCL: R414.2, U4.1
PMIC_SDA: R415.2, U4.2
PMIC_SLEEP: U1.AF23, U4.49, U10.A1
PMIC_SW1: L401.1, U4.12
PMIC_SW2: L402.1, U4.9
PMIC_SW3: L403.1, U4.25
PMIC_SW4: L404.1, U4.65
PMIC_SW5: L405.1, U4.53
PMIC_VDC: C410.1, R410.2, R411.1, U4.61
PMIC_VREF: C413.1, U4.46
RECOVERY_ADC: R1504.1, TP10.1, U1.D26
RESET_N: C411.1, R412.2, R1103.1, R1507.2, TP9.1, U1.1P12, U4.67, U16.2
SOC_EMMC_CLK: R8004.1, U1.M25
SOC_USB_RX_N: U1.AB27, U6.10
SOC_USB_RX_P: U1.AB26, U6.9
SOC_USB_TX_N: U1.AD27, U6.7
SOC_USB_TX_P: U1.AD26, U6.6
SOC_VBUS_DET: C1503.1, R1505.2, R1506.1, U1.1P14
SYS_3V3_PG: R1301.1, TP14.1, U17.4
SYS_SS: C1303.1, U17.9
SYS_SW: L1301.1, U17.1, U17.2, U17.3
THERMAL_SHUTDOWN: R1507.1, U1.1R13
USB_AVDD_0V9: C1679.1, C1680.1, R1601.2, U1.1L14
USB_AVDD_1V8: C1681.1, C1682.1, R1602.2, U1.1M15
USB_CC1: J1.A5, U6.2, U9.4
USB_CC2: J1.B5, U6.1, U9.5
USB_CC_ENABLE_N: U6.29, U13.4
USB_CURRENT_OK: U14.4, U19.1
USB_DM: J1.A7, J1.B7, U1.AF26, U9.2
USB_DP: J1.A6, J1.B6, U1.AF27, U9.1
USB_DVDT: C1202.1, U15.1
USB_ILIM: R1201.1, U15.7
USB_MAIN_ENABLE: R1102.1, U15.2, U19.4
USB_MUX_ENABLE_N: U6.12, U16.4
USB_ORIENTATION: R602.2, U6.11
USB_POWER_FAULT_N: R1202.1, TP13.1, U15.6
USB_RX1_N: J1.B10, U6.14, U7.5
USB_RX1_P: J1.B11, U6.15, U7.4
USB_RX2_N: J1.A10, U6.18, U8.5
USB_RX2_P: J1.A11, U6.19, U8.4
USB_TX1_N: C602.2, J1.A3, U7.2
USB_TX1_P: C601.2, J1.A2, U7.1
USB_TX2_N: C604.2, J1.B3, U8.2
USB_TX2_P: C603.2, J1.B2, U8.1
VBUS_GUARD_DVDT: C1903.1, U24.18
VBUS_GUARD_ILIM: R1905.1, U24.17
VBUS_OVP: R1903.2, R1904.1, U24.15
VBUS_PROTECTED: C605.1, C1101.1, C1201.1, C1902.1, R601.1, U6.30, U11.1, U11.3, U15.3, U15.4, U24.4, U24.5, U24.6, U24.7, U24.8
VBUS_RAW: C1901.1, J1.A4, J1.A9, J1.B4, J1.B9, R1901.1, R1903.1, TP2.1, U24.9, U24.10, U24.11, U24.12, U24.13
VBUS_UVLO: R1901.2, R1902.1, U24.14
VCCA1V8_IMAGE: C468.1, U1.1M7, U1.1M8, U1.1N9, U4.6
VCCA1V8_PMU: C467.1, C1631.1, C1632.1, U1.1L13, U4.5
VCCA_1V8: C466.1, C1635.1, C1636.1, C1644.1, C1645.1, R1504.2, R1602.1, U1.1E14, U1.1E15, U1.1G1, U1.1K2, U1.1K15, U4.3
VCCIO_ACODEC: C463.1, U4.28
VCCIO_SD: C464.1, U4.29
VDDA0V9_IMAGE: C460.1, U1.1L6, U1.1L8, U1.1M9, U4.23
VDDA0V9_PMU: C462.1, C1629.1, C1630.1, U1.1M11, U1.1M13, U4.20
VDDA_0V9: C461.1, C1633.1, C1634.1, C1642.1, C1643.1, R1601.1, U1.1K14, U1.1M10, U4.21
VDD_CPU: C1011.1, C1012.1, C1013.1, C1014.1, C1020.1, C1601.1, C1602.1, C1603.1, C1604.1, C1605.1, C1606.1, C1607.1, C1608.1, L1001.2, R1001.1, TP8.1, U1.1G8, U1.1H6, U1.1H7, U1.1H8, U1.1J6, U1.1J7
VDD_GPU: C432.1, C442.1, C452.1, C1616.1, C1617.1, C1618.1, C1619.1, C1620.1, L402.2, R422.1, U1.1E12, U1.1F11, U1.1F12, U1.1F13, U1.1G11, U1.1G12
VDD_GPU_COM: C452.2, R422.2, U4.8
VDD_LOGIC: C431.1, C441.1, C451.1, C1609.1, C1610.1, C1611.1, C1612.1, C1613.1, C1614.1, C1615.1, L401.2, R421.1, U1.1G10, U1.1H10, U1.1H11, U1.1J10, U1.1J11, U1.1J12, U1.1K10
VDD_LOGIC_COM: C451.2, R421.2, U4.13
VDD_NPU: C434.1, C444.1, C454.1, C1621.1, C1622.1, C1623.1, C1624.1, L404.2, R424.1, U1.1G3, U1.1G4, U1.1G5, U1.1H3, U1.1H4
VDD_NPU_COM: C454.2, R424.2, U4.64
WIFI_ANT: J2001.1, R2001.2
WIFI_BUCK_OUT: C2003.1, L2001.2, U25.23
WIFI_BUCK_SW: L2001.1, U25.21
WIFI_CLK: U1.U25, U25.17
WIFI_CMD: R2014.1, U1.T27, U25.16
WIFI_D0: R2010.1, U1.U26, U25.18
WIFI_D1: R2011.1, U1.V25, U25.19
WIFI_D2: R2012.1, U1.T25, U25.14
WIFI_D3: R2013.1, U1.T26, U25.15
WIFI_HOST_WAKE: U1.V26, U25.13
WIFI_LPO: R2003.2, U25.24
WIFI_LPO_SRC: R2003.1, Y2001.3
WIFI_REG_ON: R2002.1, U1.1J14, U25.12
WIFI_RF: R2001.1, U25.2
WIFI_VBAT: C2001.1, C2002.1, FB2001.2, U25.9
WIFI_VBAT_FB: R2202.2, R2203.1, U26.5
WIFI_VBAT_PG: R2201.1, U17.13, U26.4
WIFI_VBAT_SS: C2203.1, U26.9
WIFI_VBAT_SW: L2201.1, U26.1, U26.2, U26.3
WIFI_XIN: C2008.1, U25.10, Y2002.1
WIFI_XOUT: R2004.1, U25.11
WIFI_XTAL_OUT: C2009.1, R2004.2, Y2002.3
XIN24M: C1501.1, R1502.2, U1.AG25, Y1.1
XOUT24M: R1501.1, R1502.1, U1.AF25
XTAL24_DRIVE: C1502.1, R1501.2, Y1.3
